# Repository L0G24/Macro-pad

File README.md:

# **Macropad — Volume + Macro Controller**

##### This is my custom macropad built for Hack Club Blueprint.

##### It’s a small desk controller that lets me:

* ###### Control volume with a rotary encoder

###### 

* ###### Play / pause with encoder press

###### 

* ###### Use shortcut keys (Chrome, Copy, Paste, LED mode, minimize app)

###### 

* ###### Show animations + volume on an OLED

###### 

* ###### Control RGB effects with presets using one of the keys

###### I designed the PCB in KiCad, modeled the case in Fusion, and programmed it using KMK.

### **🖼️ Screenshots**

###### 

* #### Overall Hackpad

#### 

* #### Schematic

#### 

* #### PCB Layout

#### 

* #### Case + How It Fits Together

###### 

###### 

## ***🧩 Features***

###### 

* #### 5 mechanical keys

#### 

* #### EC11 rotary encoder with push

#### 

* #### SSD1306 0.91" OLED (128×32)

#### 

* #### 10x SK6812 mini RGB LEDs (underglow)

#### 

* #### USB HID (macros + media control)

#### 

* #### Animation when idle, volume overlay when adjusting

#### 

* #### LED presets controlled by a key

###### 

## ***🧾 Parts List***

#### **Part 				                  Quantity		   Notes**

#### Seeed XIAO RP2040  		             1			     Main controller

#### MX mechanical switches	  	         5			     With keycaps

#### EC11 rotary encoder		             1			     With push button

#### SSD1306 OLED, 0.91", 4-pin	         1			     I2C (GND-VCC-SCL-SDA)

#### SK6812 MINI-E LEDs		              10			     Addressable RGB

#### 1N4148 diodes			                 5			     One per switch

#### M3 heat-set inserts		             2		       For mounting

#### M3×16mm screws	                     2           For PCB mounting

#### 3D printed case + plate	           1	         Custom Fusion design

## **⚙️ Firmware**

###### 

##### **Framework: KMK**

###### 

### **Functions:**

###### 

##### Volume up/down (encoder)

##### 

##### Play / pause (encoder press)

##### 

##### Chrome launch

##### 

##### Copy / Paste

##### 

##### LED mode toggle

##### 

##### Minimize apps

#####

##### Idle animation resumes after volume change

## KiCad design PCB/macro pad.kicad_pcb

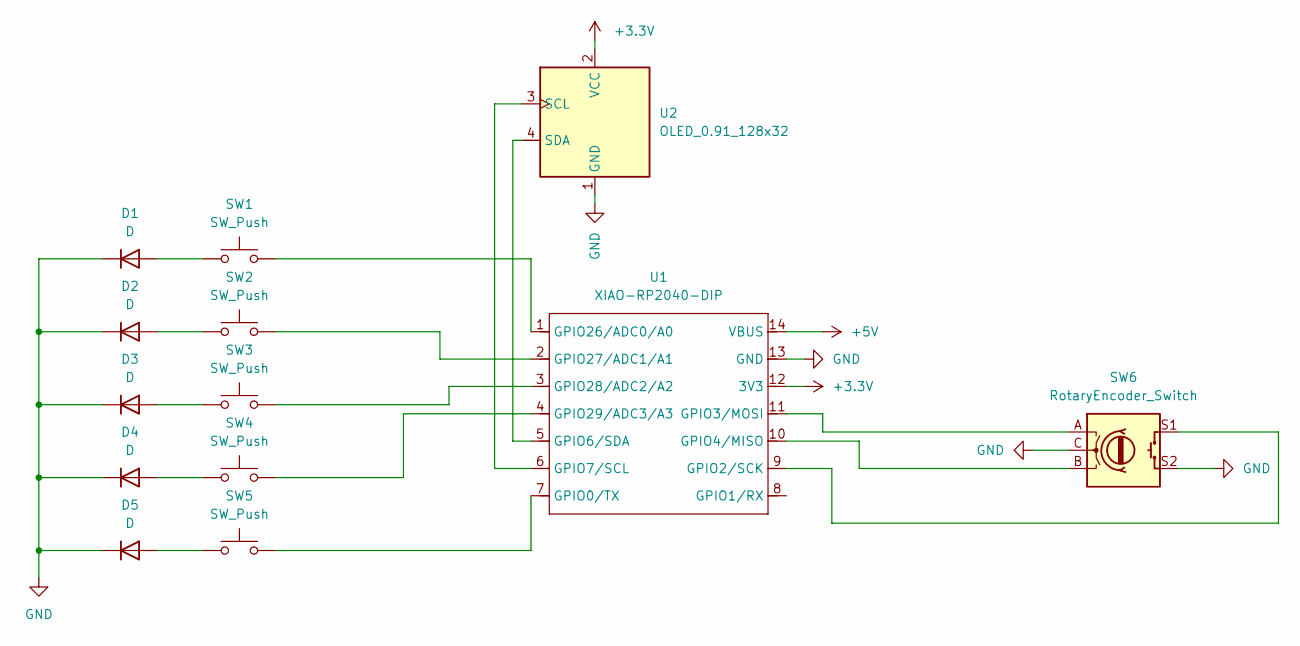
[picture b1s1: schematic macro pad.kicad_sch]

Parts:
D1, D2, D3, D4, D5: D; D_A-405_P10.16mm_Horizontal
SW1, SW2, SW3, SW4, SW5: SW_Push; SW_Cherry_MX_1.00u_PCB
SW6: RotaryEncoder_Switch; RotaryEncoder_Alps_EC11E-Switch_Vertical_H20mm
U1: XIAO-RP2040-DIP
U2: OLED_0.91_128x32

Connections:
+3.3V: U1.12 (3V3), U2.2 (VCC)
+5V: U1.14 (VBUS)
GND: D1.1 (K), D2.1 (K), D3.1 (K), D4.1 (K), D5.1 (K), SW6.C, SW6.S2, U1.13 (GND), U2.1 (GND)
unnamed: D1.2 (A), SW1.1
unnamed: D2.2 (A), SW2.1
unnamed: D3.2 (A), SW3.1
unnamed: D4.2 (A), SW4.1
unnamed: D5.2 (A), SW5.1
unnamed: SW5.2, U1.7 (GPIO0/TX)
unnamed: SW6.S1, U1.9 (GPIO2/SCK)
unnamed: SW6.A, U1.11 (GPIO3/MOSI)
unnamed: SW6.B, U1.10 (GPIO4/MISO)
unnamed: U1.5 (GPIO6/SDA), U2.4 (SDA)
unnamed: U1.6 (GPIO7/SCL), U2.3 (SCL)
unnamed: SW1.2, U1.1 (GPIO26/ADC0/A0)
unnamed: SW2.2, U1.2 (GPIO27/ADC1/A1)
unnamed: SW3.2, U1.3 (GPIO28/ADC2/A2)
unnamed: SW4.2, U1.4 (GPIO29/ADC3/A3)

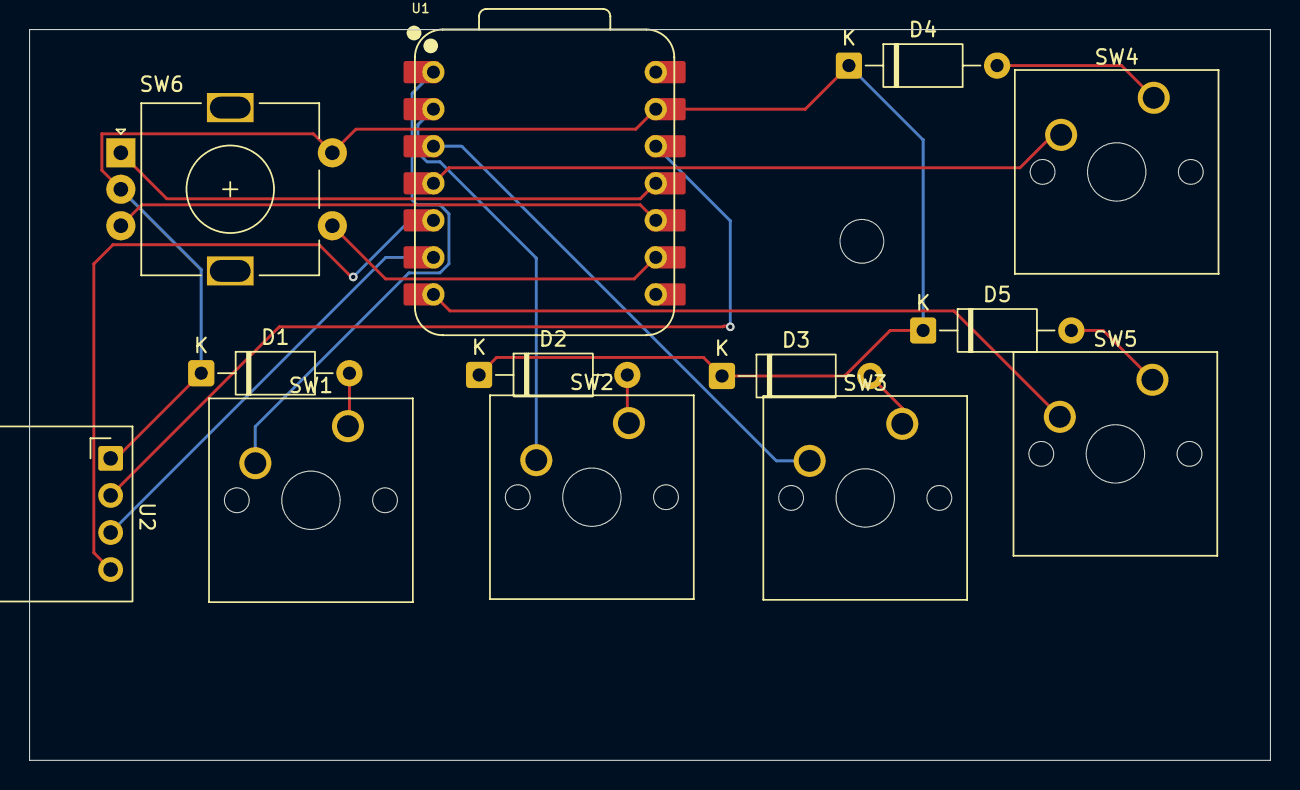
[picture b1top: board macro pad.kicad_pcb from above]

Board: 2 copper layers, 85.1 x 50.1 mm, 13 parts (0 on the bottom side), 17 nets.

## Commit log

2026-03-07 Rename macro_pcb_layout.png to macropad_pcb_layout.png
